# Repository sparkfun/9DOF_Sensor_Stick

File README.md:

SparkFun 9 Degrees of Freedom - Sensor Stick
=============================================

[*SparkFun 9 Degrees of Freedom - Sensor Stick (SEN-13944)*](https://www.sparkfun.com/products/13944)

The SparkFun 9DOF Sensor Stick is a very small sensor board with 9 degrees of freedom.
It includes the LSM9DS1 with a simple I2C interface and a mounting hole for attaching it to your project.
Also, the board is a mere 0.9" in length, 0.4" in width, and 0.036" thick (0.093" overall), allowing it to be easily mounted in just about any application.
 
 Repository Contents
-------------------
* **/Hardware** - All Eagle design files (.brd, .sch)

Documentation
--------------

* **[Installing an Arduino Library Guide](https://learn.sparkfun.com/tutorials/installing-an-arduino-library)** - Basic information on how to install an Arduino library.
* **[Library](https://github.com/sparkfun/SparkFun_LSM9DS1_Arduino_Library)** - Arduino library for the 9DoF Sensor Stick.
* **[Hookup Guide](https://learn.sparkfun.com/tutorials/9dof-sensor-stick-hookup-guide)** - Basic hookup guide for the 9DoF Sensor Stick.
 
License Information
-------------------
The hardware is released under [Creative Commons ShareAlike 4.0 International](https://creativecommons.org/licenses/by-sa/4.0/).
The code is beerware; if you see me (or any other SparkFun employee) at the local, and you've found our code helpful, please buy us a round!

Distributed as-is; no warranty is given.

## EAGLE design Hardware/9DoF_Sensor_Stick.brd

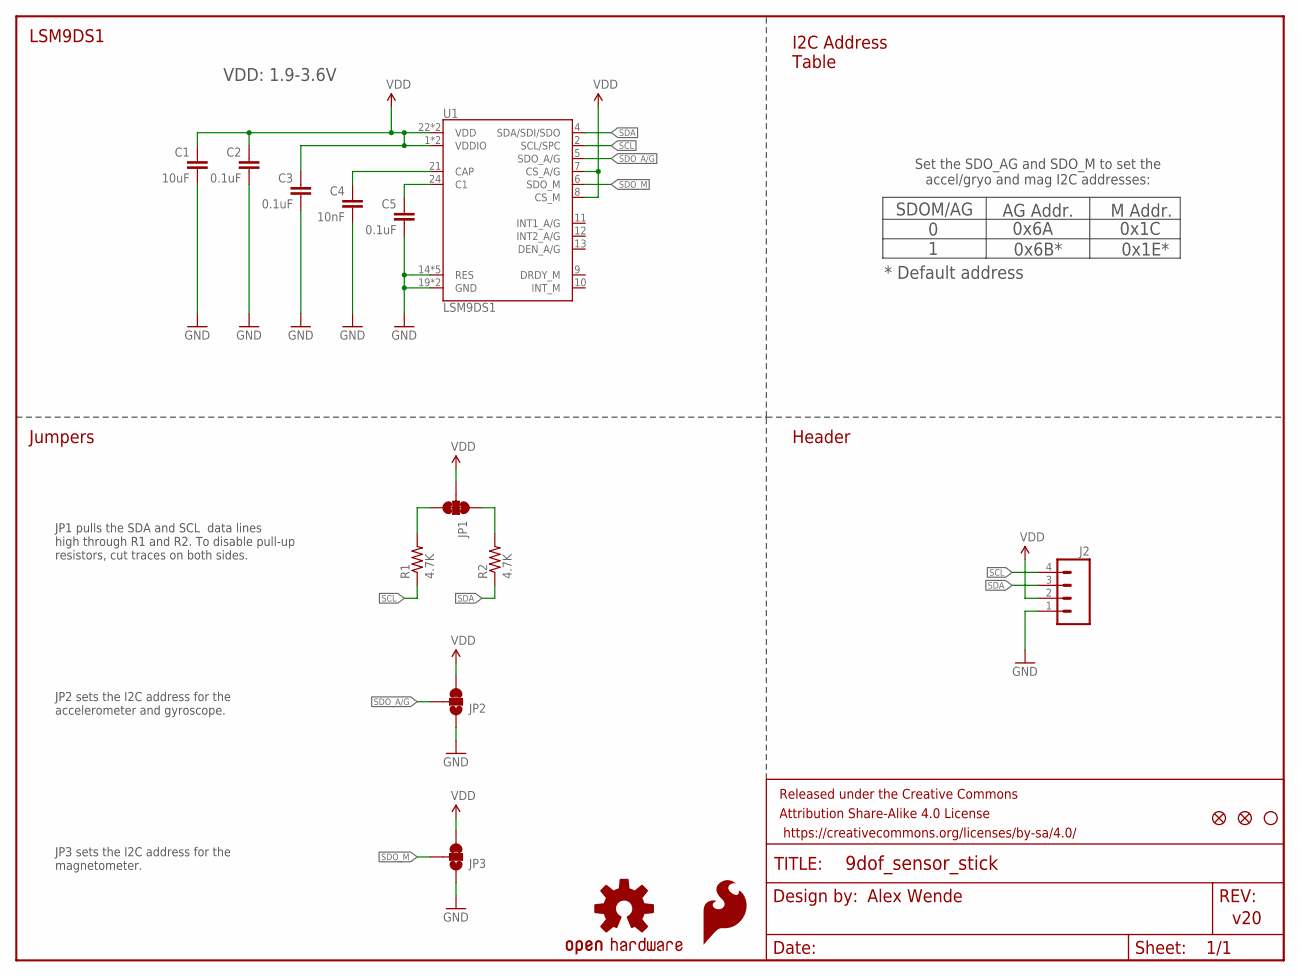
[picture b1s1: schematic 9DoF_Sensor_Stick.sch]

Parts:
C1: 10uF; 0603-CAP
C2, C3, C5: 0.1uF; 0603-CAP
C4: 10nF; 0603-CAP
FD3, FD4: FIDUCIALUFIDUCIAL; MICRO-FIDUCIAL
FRAME1: FRAME-LETTER; CREATIVE_COMMONS
H1: STAND-OFF
J2: M04NO_SILK_ALL_ROUND; 1X04_NO_SILK_ALL_ROUND
JP1: JUMPER-PAD-3-NC_BY_TRACE; PAD-JUMPER-3-3OF3_NC_BY_TRACE_YES_SILK_FULL_BOX
JP2, JP3: JUMPER-PAD-3-2OF3_NC_BY_TRACE_SMALL; PAD-JUMPER-3-2OF3_NC_BY_TRACE_YES_SILK_FULL_BOX
LOGO1: SFE_LOGO_FLAME.1_INCH; SFE_LOGO_FLAME_.1
LOGO3: OSHW-LOGOMINI; OSHW-LOGO-MINI
R1, R2: 4.7K; 0603-RES
U1: LSM9DS1; LGA24-8X4

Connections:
GND: C1.2, C2.2, C3.2, C4.2, C5.2, J2.1, JP2.1, JP3.1, U1.14 (RES), U1.15 (RES), U1.16 (RES), U1.17 (RES), U1.18 (RES), U1.19 (GND), U1.20 (GND)
unnamed: JP1.1, R2.2
unnamed: JP1.3, R1.2
unnamed: C4.1, U1.21 (CAP)
unnamed: C5.1, U1.24 (C1)
SCL: J2.4, R1.1, U1.2 (SCL/SPC)
SDA: J2.3, R2.1, U1.4 (SDA/SDI/SDO)
SDO_A/G: JP2.2, U1.5 (SDO_A/G)
SDO_M: JP3.2, U1.6 (SDO_M)
VDD: C1.1, C2.1, C3.1, J2.2, JP1.2, JP2.3, JP3.3, U1.1 (VDDIO), U1.3 (VDDIO), U1.7 (CS_A/G), U1.8 (CS_M), U1.22 (VDD), U1.23 (VDD)

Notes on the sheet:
Alex Wende
v20
LSM9DS1
SDOM/AG
AG Addr.
0 1
M Addr.
Set the SDO_AG and SDO_M to set the accel/gryo and mag I2C addresses:
I2C Address Table
Header
Jumpers
JP1 pulls the SDA and SCL data lines high through R1 and R2. To disable pull-up resistors, cut traces on both sides.
JP2 sets the I2C address for the accelerometer and gyroscope.
JP3 sets the I2C address for the magnetometer.
0x6A
0x6B*
0x1C
0x1E*
* Default address
VDD: 1.9-3.6V

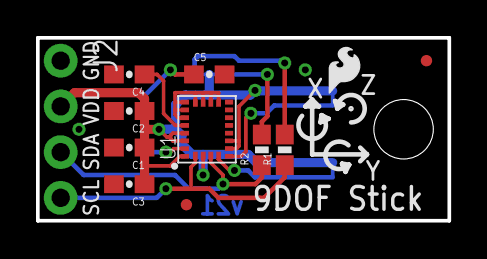
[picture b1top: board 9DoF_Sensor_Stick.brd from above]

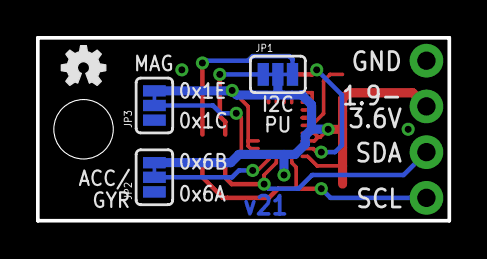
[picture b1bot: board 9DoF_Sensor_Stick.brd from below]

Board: 2 copper layers, 22.9 x 10.2 mm, 18 parts (4 on the bottom side), 10 nets.

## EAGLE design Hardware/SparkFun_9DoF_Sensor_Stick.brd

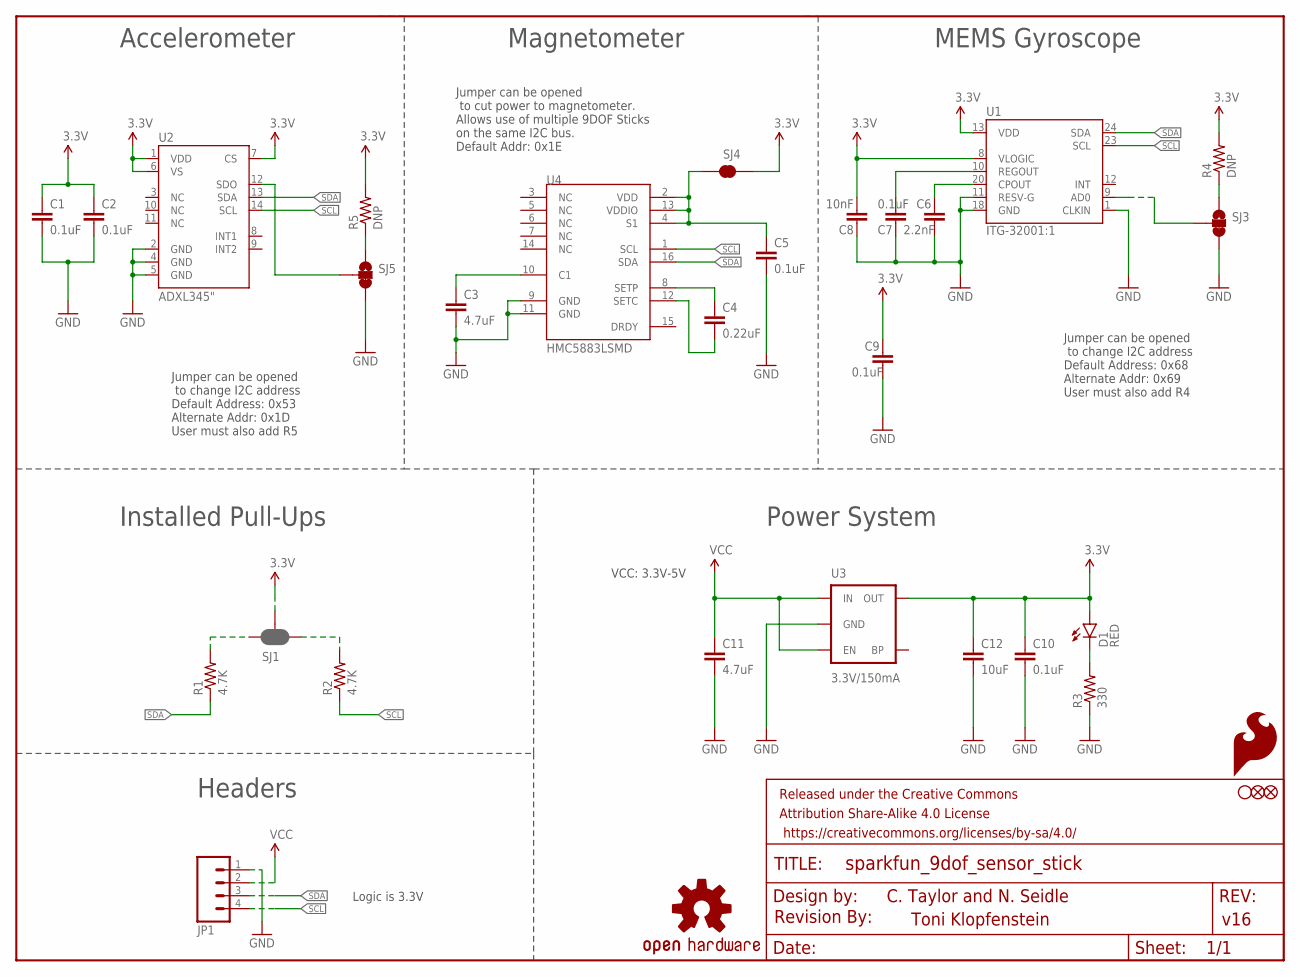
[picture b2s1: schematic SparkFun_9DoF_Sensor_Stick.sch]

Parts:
C1, C2, C5, C7, C9, C10: 0.1uF; 0603-CAP
C3, C11: 4.7uF; 0603-CAP
C4: 0.22uF; 0603-CAP
C6: 2.2nF; 0603-CAP
C8: 10nF; 0603-CAP
C12: 10uF; 0603-CAP
D1: RED; LED-0603
FRAME1: FRAME-LETTER; CREATIVE_COMMONS
JP1: M04PTH; 1X04
JP2, JP3: FIDUCIALUFIDUCIAL; MICRO-FIDUCIAL
JP4: SFE_LOGO_FLAME.1_INCH; SFE_LOGO_FLAME_.1
JP5: STAND-OFF
R1, R2: 4.7K; 0603-RES
R3: 330; 0603-RES
R4, R5: DNP; 0603-RES
SJ1: JUMPER-PAD-3-NC_BY_PASTE; PAD-JUMPER-3-NC_BY_PASTE_YES_SILK_FULL_BOX
SJ3, SJ5: JUMPER-PAD-3-2OF3_NC_BY_TRACE_LARGE; PAD-JUMPER-3-2OF3_NC_BY_TRACE_YES_SILK_LARGE
SJ4: JUMPER-PAD-2-NC_BY_TRACE; PAD-JUMPER-2-NC_BY_TRACE_YES_SILK
U1: ITG-32001:1; QFN-24_ITG3200_1:1
U2: ADXL345"; ADXL3451:1
U3: 3.3V/150mA; SOT23-5
U4: HMC5883LSMD; 16LPCC
U$3: OSHW-LOGOS; OSHW-LOGO-S
U$4: REVISION

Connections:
3.3V: C1.1, C2.1, C8.1, C9.1, C10.1, C12.1, D1.A, R4.2, R5.2, SJ1.2, SJ4.1, U1.8 (VLOGIC), U1.13 (VDD), U2.1 (VDD), U2.6 (VS), U2.7 (CS), U3.5 (OUT)
GND: C1.2, C2.2, C3.2, C5.2, C6.2, C7.2, C8.2, C9.2, C10.2, C11.2, C12.2, JP1.1, R3.1, SJ3.3, SJ5.3, U1.1 (CLKIN), U1.11 (RESV-G), U1.18 (GND), U2.2 (GND), U2.4 (GND), U2.5 (GND), U3.2 (GND), U4.9 (GND), U4.11 (GND)
unnamed: C3.1, U4.10 (C1)
unnamed: C4.1, U4.8 (SETP)
unnamed: C4.2, U4.12 (SETC)
unnamed: D1.C, R3.2
unnamed: C6.1, U1.20 (CPOUT)
unnamed: R1.2, SJ1.3
unnamed: C7.1, U1.10 (REGOUT)
unnamed: R2.2, SJ1.1
unnamed: SJ3.2, U1.9 (AD0)
unnamed: SJ5.2, U2.12 (SDO)
unnamed: R4.1, SJ3.1
unnamed: C5.1, SJ4.2, U4.2 (VDD), U4.4 (S1), U4.13 (VDDIO)
unnamed: R5.1, SJ5.1
SCL: JP1.4, R2.1, U1.23 (SCL), U2.14 (SCL), U4.1 (SCL)
SDA: JP1.3, R1.1, U1.24 (SDA), U2.13 (SDA), U4.16 (SDA)
VCC: C11.1, JP1.2, U3.1 (IN), U3.3 (EN)

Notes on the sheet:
Installed Pull-Ups
C. Taylor and N. Seidle
Toni Klopfenstein
v16
Accelerometer
Magnetometer
MEMS Gyroscope
Power System
Headers
VCC: 3.3V-5V
Logic is 3.3V
Jumper can be opened to change I2C address Default Address: 0x53 Alternate Addr: 0x1D User must also add R5
Jumper can be opened to change I2C address Default Address: 0x68 Alternate Addr: 0x69 User must also add R4
Jumper can be opened to cut power to magnetometer. Allows use of multiple 9DOF Sticks on the same I2C bus. Default Addr: 0x1E

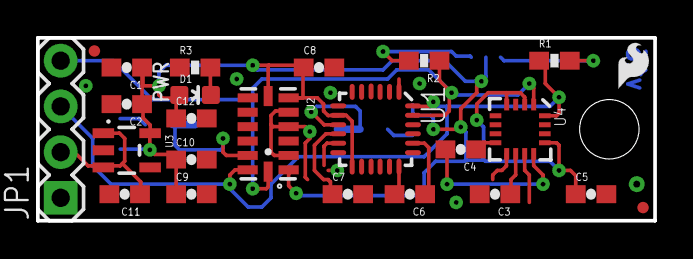
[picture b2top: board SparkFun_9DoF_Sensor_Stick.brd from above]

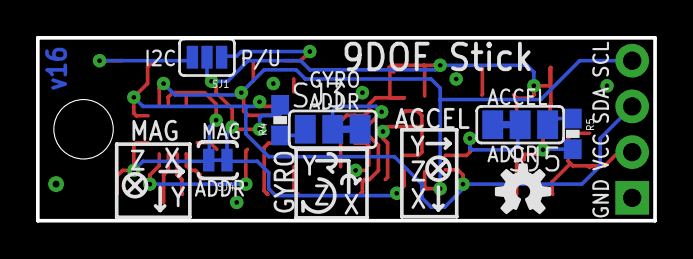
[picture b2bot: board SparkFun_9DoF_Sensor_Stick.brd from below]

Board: 2 copper layers, 34.3 x 10.2 mm, 34 parts (7 on the bottom side), 18 nets.

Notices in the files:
parts and their libraries:
SparkFun-Capacitors: Licensing: Creative Commons ShareAlike 4.0 International - https://creativecommons.org/licenses/by-sa/4.0
SparkFun-Aesthetics: Released under the Creative Commons Attribution Share-Alike 4.0 License
SparkFun-Aesthetics: Released under the Creative Commons
